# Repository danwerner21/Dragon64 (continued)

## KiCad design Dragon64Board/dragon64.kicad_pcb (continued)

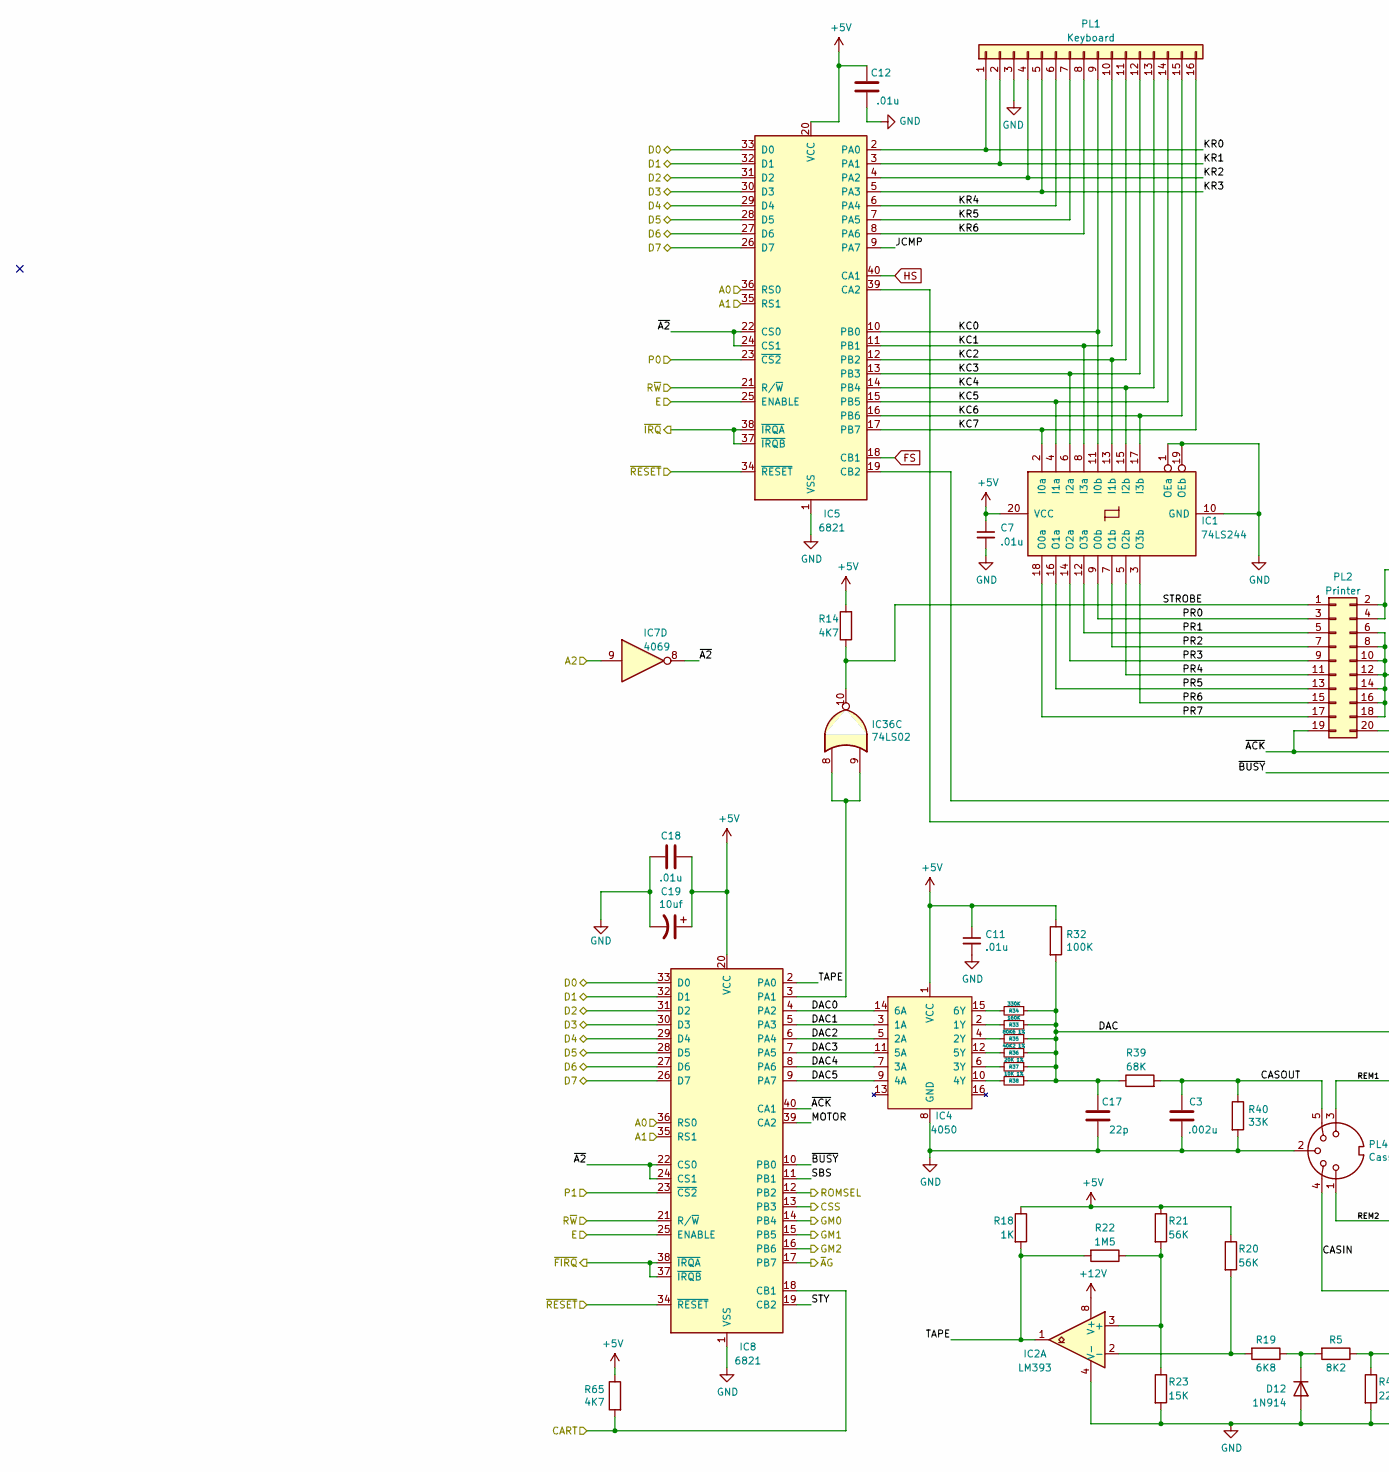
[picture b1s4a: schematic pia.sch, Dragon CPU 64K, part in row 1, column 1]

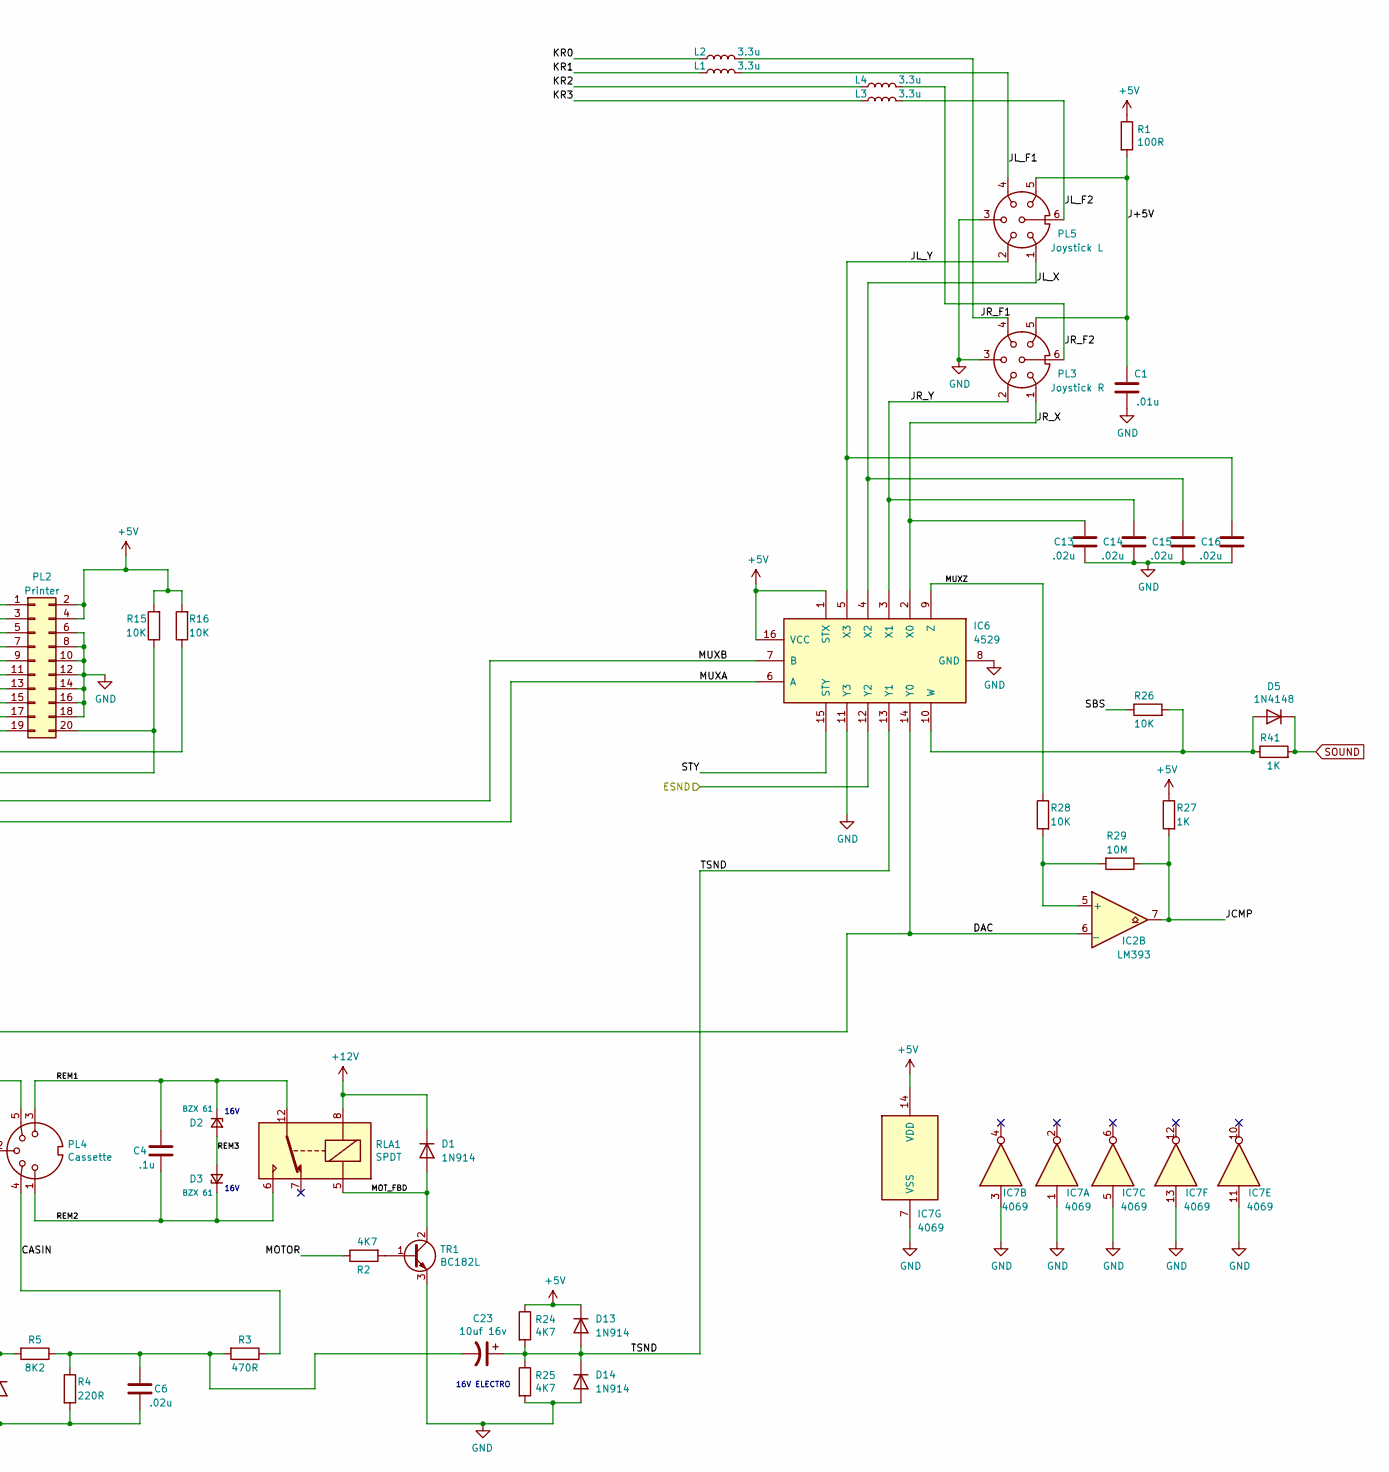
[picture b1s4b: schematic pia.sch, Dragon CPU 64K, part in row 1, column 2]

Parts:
C1, C7, C11, C12, C18: .01u; C_Disc_D7.5mm_W2.5mm_P5.00mm
C3: .002u; C_Disc_D7.5mm_W2.5mm_P5.00mm
C4: .1u; C_Disc_D7.5mm_W2.5mm_P5.00mm
C6, C13, C14, C15, C16: .02u; C_Disc_D7.5mm_W2.5mm_P5.00mm
C17: 22p; C_Disc_D7.5mm_W2.5mm_P5.00mm
C19: 10uf; CP_Radial_D4.0mm_P2.00mm
C23: 10uf 16v; CP_Radial_D4.0mm_P2.00mm
D1, D12, D13, D14: 1N914; D_DO-35_SOD27_P7.62mm_Horizontal
D2, D3: BZX 61; D_DO-35_SOD27_P7.62mm_Horizontal
D5: 1N4148; D_DO-35_SOD27_P7.62mm_Horizontal
IC1: 74LS244; DIP-20_W7.62mm_Socket_LongPads
IC2: LM393; DIP-8_W7.62mm_Socket_LongPads
IC4: 4050; DIP-16_W7.62mm_Socket_LongPads
IC5, IC8: 6821; DIP-40_W15.24mm_Socket_LongPads
IC6: 4529; DIP-16_W7.62mm_Socket_LongPads
IC7: 4069; DIP-14_W7.62mm_Socket_LongPads
IC36: 74LS02; DIP-14_W7.62mm_Socket_LongPads
L1, L2, L3, L4: 3.3u; L_Axial_L5.3mm_D2.2mm_P7.62mm_Horizontal_Vishay_IM-1
PL1: Keyboard; PinHeader_1x16_P2.54mm_Vertical
PL2: Printer; IDC-Header_2x10-1MP_P2.54mm_Latch_Horizontal
PL3: Joystick R; DIN-6_DELTRON_671-0601_Horizontal
PL4: Cassette; DIN-5_DELTRON_671-0501_45deg_Horizontal
PL5: Joystick L; DIN-6_DELTRON_671-0601_Horizontal
R1: 100R; R_Axial_DIN0207_L6.3mm_D2.5mm_P7.62mm_Horizontal
R2, R14, R24, R25, R65: 4K7; R_Axial_DIN0207_L6.3mm_D2.5mm_P7.62mm_Horizontal
R3: 470R; R_Axial_DIN0207_L6.3mm_D2.5mm_P7.62mm_Horizontal
R4: 220R; R_Axial_DIN0207_L6.3mm_D2.5mm_P7.62mm_Horizontal
R5: 8K2; R_Axial_DIN0207_L6.3mm_D2.5mm_P7.62mm_Horizontal
R15, R16, R26, R28: 10K; R_Axial_DIN0207_L6.3mm_D2.5mm_P7.62mm_Horizontal
R18, R27, R41: 1K; R_Axial_DIN0207_L6.3mm_D2.5mm_P7.62mm_Horizontal
R19: 6K8; R_Axial_DIN0207_L6.3mm_D2.5mm_P7.62mm_Horizontal
R20, R21: 56K; R_Axial_DIN0207_L6.3mm_D2.5mm_P7.62mm_Horizontal
R22: 1M5; R_Axial_DIN0207_L6.3mm_D2.5mm_P7.62mm_Horizontal
R23: 15K; R_Axial_DIN0207_L6.3mm_D2.5mm_P7.62mm_Horizontal
R29: 10M; R_Axial_DIN0207_L6.3mm_D2.5mm_P7.62mm_Horizontal
R32: 100K; R_Axial_DIN0207_L6.3mm_D2.5mm_P7.62mm_Horizontal
R33: 160K; R_Axial_DIN0207_L6.3mm_D2.5mm_P7.62mm_Horizontal
R34: 330K; R_Axial_DIN0207_L6.3mm_D2.5mm_P7.62mm_Horizontal
R35: 80K6 1%; R_Axial_DIN0207_L6.3mm_D2.5mm_P7.62mm_Horizontal
R36: 40K2 1%; R_Axial_DIN0207_L6.3mm_D2.5mm_P7.62mm_Horizontal
R37: 20K 1%; R_Axial_DIN0207_L6.3mm_D2.5mm_P7.62mm_Horizontal
R38: 10K 1%; R_Axial_DIN0207_L6.3mm_D2.5mm_P7.62mm_Horizontal
R39: 68K; R_Axial_DIN0207_L6.3mm_D2.5mm_P7.62mm_Horizontal
R40: 33K; R_Axial_DIN0207_L6.3mm_D2.5mm_P7.62mm_Horizontal
RLA1: SPDT; Relay_SPDT_HJR-4102
TR1: BC182L; TO-92

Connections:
+5V: C7.1, C11.1, C12.2, C18.2, C19.1, D13.1 (K), IC1.20 (VCC), IC4.1 (VCC), IC5.20 (VCC), IC6.1 (STX), IC6.16 (VCC), IC7.14 (VDD), IC8.20 (VCC), PL2.2, PL2.4, R1.1, R14.2, R15.2, R16.2, R18.1, R20.1, R21.1, R24.1, R27.1, R32.1, R65.1; also elsewhere on the board
+12V: D1.1 (K), IC2.8 (V+), RLA1.8; also elsewhere on the board
/ESND: IC6.12 (Y2); also elsewhere on the board
/P0: IC5.23 (~CS2); also elsewhere on the board
/P1: IC8.23 (~CS2); also elsewhere on the board
/PIAs/CASIN: PL4.4, R3.1
/PIAs/CASOUT: C3.2, PL4.5, R39.2, R40.1
/PIAs/CSS: IC8.13 (PB3); also elsewhere on the board
/PIAs/DAC: C17.2, IC2.6 (_), IC6.14 (Y0), R32.2, R33.1, R34.1, R35.1, R36.1, R37.1, R38.1, R39.1
/PIAs/DAC0: IC4.14 (6A), IC8.4 (PA2)
/PIAs/DAC1: IC4.3 (1A), IC8.5 (PA3)
/PIAs/DAC2: IC4.5 (2A), IC8.6 (PA4)
/PIAs/DAC3: IC4.11 (5A), IC8.7 (PA5)
/PIAs/DAC4: IC4.7 (3A), IC8.8 (PA6)
/PIAs/DAC5: IC4.9 (4A), IC8.9 (PA7)
/PIAs/GM0: IC8.14 (PB4); also elsewhere on the board
/PIAs/GM1: IC8.15 (PB5); also elsewhere on the board
/PIAs/GM2: IC8.16 (PB6); also elsewhere on the board
/PIAs/J+5V: C1.2, PL3.5, PL5.5, R1.2
/PIAs/JCMP: IC2.7, IC5.9 (PA7), R27.2, R29.1
/PIAs/JL_F1: L1.2, PL5.4
/PIAs/JL_F2: L3.2, PL5.6
/PIAs/JL_X: C15.2, IC6.4 (X2), PL5.1
/PIAs/JL_Y: C16.2, IC6.5 (X3), PL5.2
/PIAs/JR_F1: L2.2, PL3.4
/PIAs/JR_F2: L4.2, PL3.6
/PIAs/JR_X: C13.2, IC6.2 (X0), PL3.1
/PIAs/JR_Y: C14.2, IC6.3 (X1), PL3.2
/PIAs/KC0: IC1.11 (I0b), IC5.10 (PB0), PL1.9
/PIAs/KC1: IC1.8 (I3a), IC5.11 (PB1), PL1.10
/PIAs/KC2: IC1.13 (I1b), IC5.12 (PB2), PL1.11
/PIAs/KC3: IC1.6 (I2a), IC5.13 (PB3), PL1.12
/PIAs/KC4: IC1.15 (I2b), IC5.14 (PB4), PL1.13
/PIAs/KC5: IC1.4 (I1a), IC5.15 (PB5), PL1.14
/PIAs/KC6: IC1.17 (I3b), IC5.16 (PB6), PL1.15
/PIAs/KC7: IC1.2 (I0a), IC5.17 (PB7), PL1.16
/PIAs/KR0: IC5.2 (PA0), L2.1, PL1.1
/PIAs/KR1: IC5.3 (PA1), L1.1, PL1.2
/PIAs/KR2: IC5.4 (PA2), L4.1, PL1.4
/PIAs/KR3: IC5.5 (PA3), L3.1, PL1.5
/PIAs/KR4: IC5.6 (PA4), PL1.6
/PIAs/KR5: IC5.7 (PA5), PL1.7
/PIAs/KR6: IC5.8 (PA6), PL1.8
/PIAs/MOTOR: IC8.39 (CA2), R2.1
/PIAs/MOT_FBD: D1.2 (A), RLA1.5, TR1.2 (C)
/PIAs/MUXA: IC5.39 (CA2), IC6.6 (A)
/PIAs/MUXB: IC5.19 (CB2), IC6.7 (B)
/PIAs/MUXZ: IC6.9 (Z), R28.1
/PIAs/PR0: IC1.9 (O0b), PL2.3
/PIAs/PR1: IC1.12 (O3a), PL2.5
/PIAs/PR2: IC1.7 (O1b), PL2.7
/PIAs/PR3: IC1.14 (O2a), PL2.9
/PIAs/PR4: IC1.5 (O2b), PL2.11
/PIAs/PR5: IC1.16 (O1a), PL2.13
/PIAs/PR6: IC1.3 (O3b), PL2.15
/PIAs/PR7: IC1.18 (O0a), PL2.17
/PIAs/REM1: C4.2, D2.1 (K), PL4.3, RLA1.12
/PIAs/REM2: C4.1, D3.1 (K), PL4.1, RLA1.6
/PIAs/REM3: D2.2 (A), D3.2 (A)
/PIAs/SBS: IC8.11 (PB1), R26.1
/PIAs/STROBE: IC36.10, PL2.1, R14.1
/PIAs/STY: IC6.15 (STY), IC8.19 (CB2)
/PIAs/TAPE: IC2.1, IC8.2 (PA0), R18.2, R22.2
/PIAs/TSND: C23.1, D13.2 (A), D14.1 (K), IC6.13 (Y1), R24.2, R25.1
/PIAs/~A2: IC5.22 (CS0), IC5.24 (CS1), IC7.8, IC8.22 (CS0), IC8.24 (CS1)
/PIAs/~ACK: IC8.40 (CA1), PL2.19, R16.1
/PIAs/~A~G: IC8.17 (PB7); also elsewhere on the board
/PIAs/~BUSY: IC8.10 (PB0), PL2.20, R15.1
/ROMSEL: IC8.12 (PB2); also elsewhere on the board
/~FIRQ: IC8.37 (~IRQB), IC8.38 (~IRQA); also elsewhere on the board
/~IRQ: IC5.37 (~IRQB), IC5.38 (~IRQA); also elsewhere on the board
A0: IC5.36 (RS0), IC8.36 (RS0); also elsewhere on the board
A1: IC5.35 (RS1), IC8.35 (RS1); also elsewhere on the board
A2: IC7.9; also elsewhere on the board
CART: IC8.18 (CB1), R65.2; also elsewhere on the board
D0: IC5.33 (D0), IC8.33 (D0); also elsewhere on the board
D1: IC5.32 (D1), IC8.32 (D1); also elsewhere on the board
D2: IC5.31 (D2), IC8.31 (D2); also elsewhere on the board
D3: IC5.30 (D3), IC8.30 (D3); also elsewhere on the board
D4: IC5.29 (D4), IC8.29 (D4); also elsewhere on the board
D5: IC5.28 (D5), IC8.28 (D5); also elsewhere on the board
D6: IC5.27 (D6), IC8.27 (D6); also elsewhere on the board
D7: IC5.26 (D7), IC8.26 (D7); also elsewhere on the board
E: IC5.25 (ENABLE), IC8.25 (ENABLE); also elsewhere on the board
FS: IC5.18 (CB1); also elsewhere on the board
GND: C1.1, C3.1, C6.1, C7.2, C11.2, C12.1, C13.1, C14.1, C15.1, C16.1, C17.1, C18.1, C19.2, D12.2 (A), D14.2 (A), IC1.1 (OEa), IC1.10 (GND), IC1.19 (OEb), IC2.4 (V-), IC4.8 (GND), IC5.1 (VSS), IC6.8 (GND), IC6.11 (Y3), IC7.1, IC7.3, IC7.5, IC7.7 (VSS), IC7.11, IC7.13, IC8.1 (VSS), PL1.3, PL2.6, PL2.8, PL2.10, PL2.12, PL2.14, PL2.16, PL2.18, PL3.3, PL4.2, PL5.3, R4.2, R23.2, R25.2, R40.2, TR1.3 (E); also elsewhere on the board
HS: IC5.40 (CA1); also elsewhere on the board
unnamed: C6.2, C23.2, R3.2, R4.1, R5.1
unnamed: D5.2 (A), IC6.10 (W), R26.2, R41.1
unnamed: D12.1 (K), R5.2, R19.1
unnamed: IC2.2 (-), R19.2, R20.2
unnamed: IC2.3 (+), R21.2, R22.1, R23.1
unnamed: IC2.5 (+), R28.2, R29.2
unnamed: IC4.2 (1Y), R33.2
unnamed: IC4.4 (2Y), R35.2
unnamed: IC4.6 (3Y), R37.2
unnamed: IC4.10 (4Y), R38.2
unnamed: IC4.12 (5Y), R36.2
unnamed: IC4.15 (6Y), R34.2
unnamed: IC8.3 (PA1), IC36.8, IC36.9
unnamed: R2.2, TR1.1 (B)
R~W~: IC5.21 (R/~W), IC8.21 (R/~W); also elsewhere on the board
SOUND: D5.1 (K), R41.2; also elsewhere on the board
~RESET: IC5.34 (~RESET), IC8.34 (~RESET); also elsewhere on the board

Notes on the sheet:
16V
16V ELECTRO

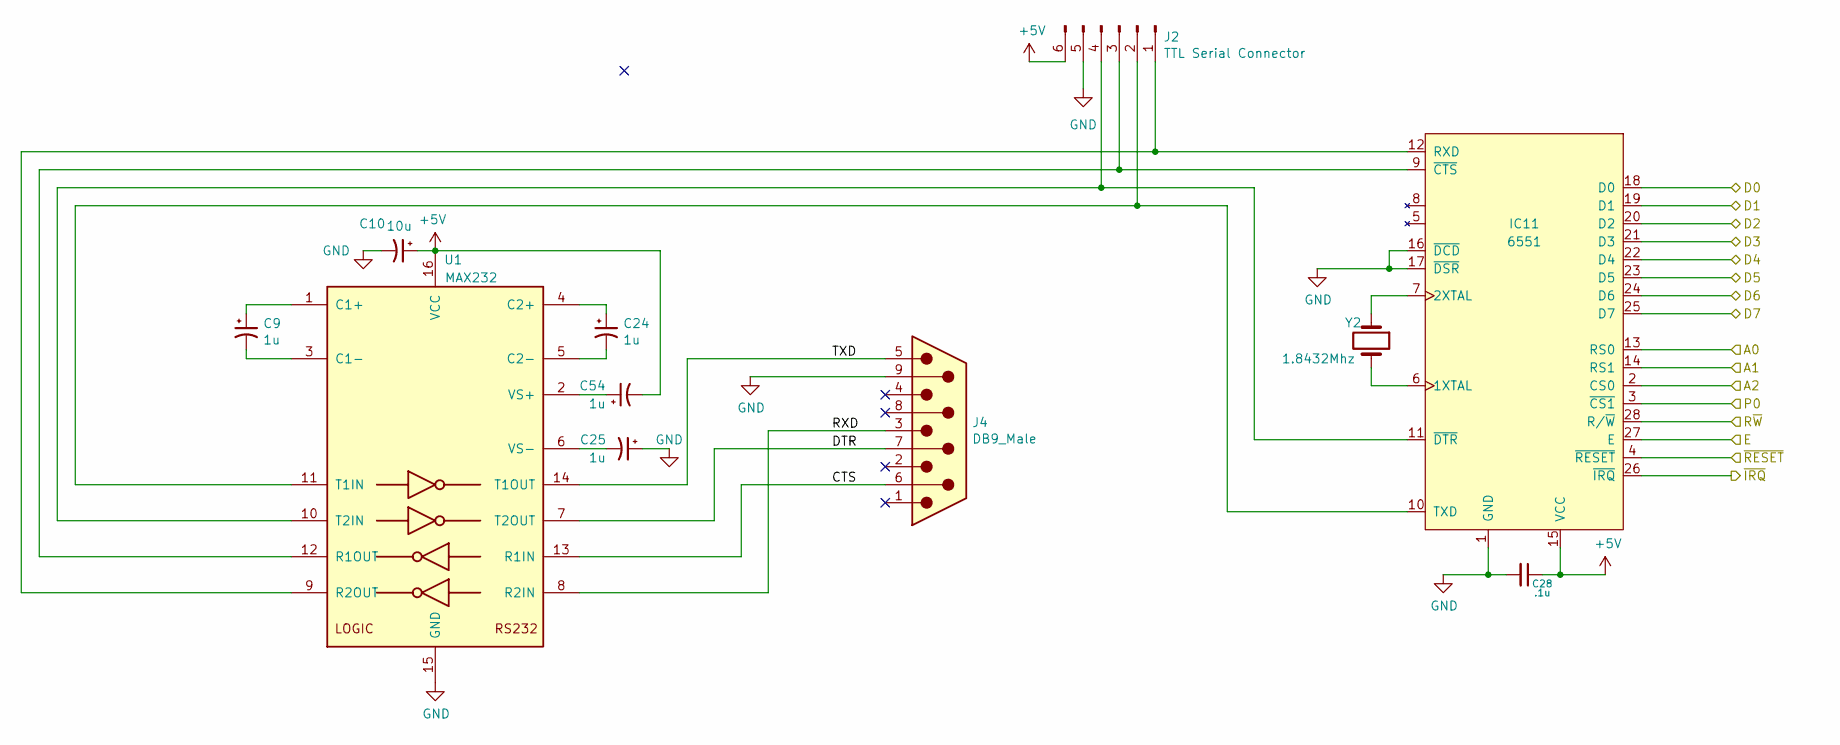
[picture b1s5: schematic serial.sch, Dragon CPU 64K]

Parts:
C9, C24, C25, C54: 1u; CP_Radial_D4.0mm_P2.00mm
C10: 10u; CP_Radial_D4.0mm_P2.00mm
C28: .1u; C_Disc_D7.5mm_W2.5mm_P5.00mm
IC11: 6551; DIP-28_W15.24mm_Socket_LongPads
J2: TTL Serial Connector; PinHeader_1x06_P2.54mm_Vertical
J4: DB9_Male; DSUB-9_Male_Horizontal_P2.77x2.84mm_EdgePinOffset4.94mm_Hou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
U1: MAX232; DIP-16_W7.62mm_Socket_LongPads
Y2: 1.8432Mhz; Crystal_HC49-U_Vertical

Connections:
+5V: C10.1, C28.1, C54.2, IC11.15 (VCC), J2.6, U1.16 (VCC); also elsewhere on the board
/P0: IC11.3 (~CS1~); also elsewhere on the board
/Serial/CTS: J4.6, U1.13 (R1IN)
/Serial/DTR: J4.7, U1.7 (T2OUT)
/Serial/RXD: J4.3, U1.8 (R2IN)
/Serial/TXD: J4.5, U1.14 (T1OUT)
/~IRQ: IC11.26 (~IRQ~); also elsewhere on the board
A0: IC11.13 (RS0); also elsewhere on the board
A1: IC11.14 (RS1); also elsewhere on the board
A2: IC11.2 (CS0); also elsewhere on the board
D0: IC11.18 (D0); also elsewhere on the board
D1: IC11.19 (D1); also elsewhere on the board
D2: IC11.20 (D2); also elsewhere on the board
D3: IC11.21 (D3); also elsewhere on the board
D4: IC11.22 (D4); also elsewhere on the board
D5: IC11.23 (D5); also elsewhere on the board
D6: IC11.24 (D6); also elsewhere on the board
D7: IC11.25 (D7); also elsewhere on the board
E: IC11.27 (E); also elsewhere on the board
GND: C10.2, C25.1, C28.2, IC11.1 (GND), IC11.16 (~DCD~), IC11.17 (~DSR~), J2.5, J4.9, U1.15 (GND); also elsewhere on the board
unnamed: C9.1, U1.1 (C1+)
unnamed: C9.2, U1.3 (C1-)
unnamed: C24.1, U1.4 (C2+)
unnamed: C24.2, U1.5 (C2-)
unnamed: C25.2, U1.6 (VS-)
unnamed: C54.1, U1.2 (VS+)
unnamed: IC11.6 (1XTAL), Y2.2
unnamed: IC11.7 (2XTAL), Y2.1
unnamed: IC11.9 (~CTS~), J2.3, U1.12 (R1OUT)
unnamed: IC11.10 (TXD), J2.2, U1.11 (T1IN)
unnamed: IC11.11 (~DTR~), J2.4, U1.10 (T2IN)
unnamed: IC11.12 (RXD), J2.1, U1.9 (R2OUT)
R~W~: IC11.28 (R/~W~); also elsewhere on the board
~RESET: IC11.4 (~RESET~); also elsewhere on the board

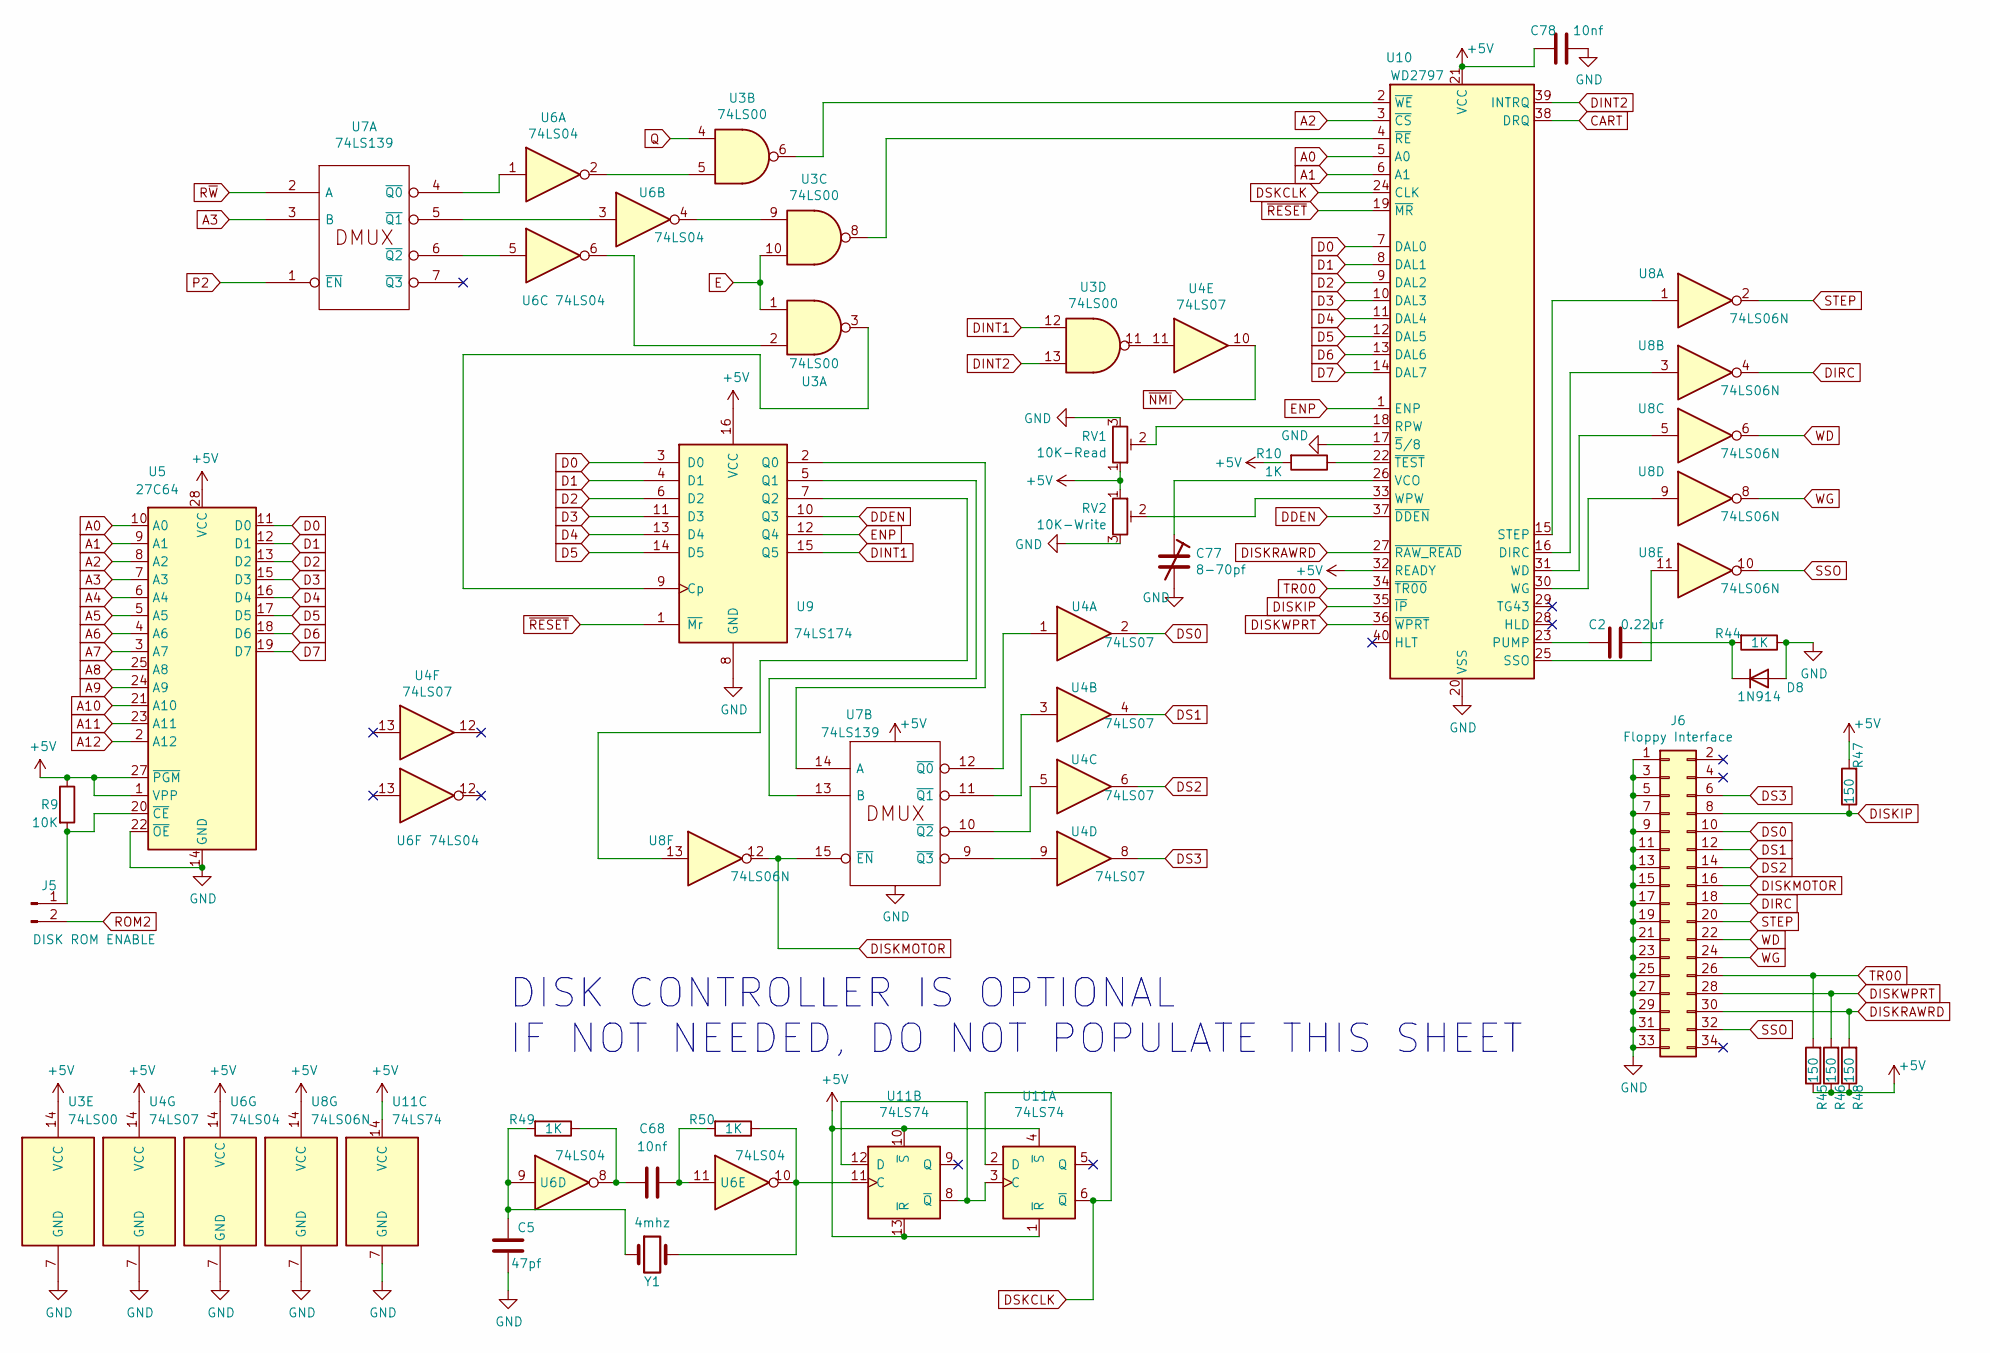
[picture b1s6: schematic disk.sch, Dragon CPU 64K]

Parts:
C2: 0.22uf; C_Disc_D7.5mm_W2.5mm_P5.00mm
C5: 47pf; C_Disc_D7.5mm_W2.5mm_P5.00mm
C68, C78: 10nf; C_Disc_D7.5mm_W2.5mm_P5.00mm
C77: 8-70pf; c_trimmer-10
D8: 1N914; D_DO-35_SOD27_P7.62mm_Horizontal
J5: DISK ROM ENABLE; PinHeader_1x02_P2.54mm_Vertical
J6: Floppy Interface; IDC-Header_2x17_P2.54mm_Vertical
R9: 10K; R_Axial_DIN0207_L6.3mm_D2.5mm_P7.62mm_Horizontal
R10, R44, R49, R50: 1K; R_Axial_DIN0207_L6.3mm_D2.5mm_P7.62mm_Horizontal
R45, R46, R47, R48: 150; R_Axial_DIN0207_L6.3mm_D2.5mm_P7.62mm_Horizontal
RV1: 10K-Read; Potentiometer_Vishay_T73YP_Vertical
RV2: 10K-Write; Potentiometer_Vishay_T73YP_Vertical
U3: 74LS00; DIP-14_W7.62mm_Socket_LongPads
U4: 74LS07; DIP-14_W7.62mm_Socket_LongPads
U5: 27C64; DIP-28_W15.24mm_Socket_LongPads
U6: 74LS04; DIP-14_W7.62mm_Socket_LongPads
U7: 74LS139; DIP-16_W7.62mm_Socket_LongPads
U8: 74LS06N; DIP-14_W7.62mm_Socket_LongPads
U9: 74LS174; DIP-16_W7.62mm_Socket_LongPads
U10: WD2797; DIP-40_W15.24mm
U11: 74LS74; DIP-14_W7.62mm_Socket_LongPads
Y1: 4mhz; Crystal_HC49-U_Vertical

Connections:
+5V: C78.2, R9.1, R10.2, R45.1, R46.1, R47.2, R48.1, RV1.1, RV2.1, U3.14 (VCC), U4.14 (VCC), U5.1 (VPP), U5.27 (~PGM), U5.28 (VCC), U6.14 (VCC), U7.16 (VCC), U8.14 (VCC), U9.16 (VCC), U10.21 (VCC), U10.32 (READY), U11.1 (~R), U11.4 (~S), U11.10 (~S), U11.13 (~R), U11.14 (VCC); also elsewhere on the board
A0: U5.10 (A0), U10.5 (A0); also elsewhere on the board
A1: U5.9 (A1), U10.6 (A1); also elsewhere on the board
A2: U5.8 (A2), U10.3 (~CS); also elsewhere on the board
A3: U5.7 (A3), U7.3 (B); also elsewhere on the board
A4: U5.6 (A4); also elsewhere on the board
A5: U5.5 (A5); also elsewhere on the board
A6: U5.4 (A6); also elsewhere on the board
A7: U5.3 (A7); also elsewhere on the board
A8: U5.25 (A8); also elsewhere on the board
A9: U5.24 (A9); also elsewhere on the board
A10: U5.21 (A10); also elsewhere on the board
A11: U5.23 (A11); also elsewhere on the board
A12: U5.2 (A12); also elsewhere on the board
CART: U10.38 (DRQ); also elsewhere on the board
D0: U5.11 (D0), U9.3 (D0), U10.7 (DAL0); also elsewhere on the board
D1: U5.12 (D1), U9.4 (D1), U10.8 (DAL1); also elsewhere on the board
D2: U5.13 (D2), U9.6 (D2), U10.9 (DAL2); also elsewhere on the board
D3: U5.15 (D3), U9.11 (D3), U10.10 (DAL3); also elsewhere on the board
D4: U5.16 (D4), U9.13 (D4), U10.11 (DAL4); also elsewhere on the board
D5: U5.17 (D5), U9.14 (D5), U10.12 (DAL5); also elsewhere on the board
D6: U5.18 (D6), U10.13 (DAL6); also elsewhere on the board
D7: U5.19 (D7), U10.14 (DAL7); also elsewhere on the board
DDEN: U9.10 (Q3), U10.37 (~DDEN)
DINT1: U3.12, U9.15 (Q5)
DINT2: U3.13, U10.39 (INTRQ)
DIRC: J6.18, U8.4
DISKIP: J6.8, R47.1, U10.35 (~IP)
DISKMOTOR: J6.16, U7.15 (~EN), U8.12
DISKRAWRD: J6.30, R48.2, U10.27 (~RAW_READ)
DISKWPRT: J6.28, R46.2, U10.36 (~WPRT)
DS0: J6.10, U4.2
DS1: J6.12, U4.4
DS2: J6.14, U4.6
DS3: J6.6, U4.8
DSKCLK: U10.24 (CLK), U11.2 (D), U11.6 (~Q)
E: U3.1, U3.10; also elsewhere on the board
ENP: U9.12 (Q4), U10.1 (ENP)
GND: C5.1, C77.2, C78.1, D8.2 (A), J6.1, J6.3, J6.5, J6.7, J6.9, J6.11, J6.13, J6.15, J6.17, J6.19, J6.21, J6.23, J6.25, J6.27, J6.29, J6.31, J6.33, R44.1, RV1.3, RV2.3, U3.7 (GND), U4.7 (GND), U5.14 (GND), U5.22 (~OE), U6.7 (GND), U7.8 (GND), U8.7 (GND), U9.8 (GND), U10.17 (~5~/8), U10.20 (VSS), U11.7 (GND); also elsewhere on the board
unnamed: C2.1, D8.1 (K), R44.2
unnamed: C2.2, U10.23 (PUMP)
unnamed: C5.2, R49.2, U6.9, Y1.1
unnamed: C68.1, R50.2, U6.11
unnamed: C68.2, R49.1, U6.8
unnamed: C77.1, U10.26 (VCO)
unnamed: J5.1, R9.2, U5.20 (~CE)
unnamed: R10.1, U10.22 (~TEST)
unnamed: R50.1, U6.10, U11.11 (C), Y1.2
unnamed: RV1.2, U10.18 (RPW)
unnamed: RV2.2, U10.33 (WPW)
unnamed: U3.2, U6.6
unnamed: U3.3, U9.9 (Cp)
unnamed: U3.5, U6.2
unnamed: U3.9, U6.4
unnamed: U3.11, U4.11
unnamed: U4.1, U7.12 (~Q0)
unnamed: U4.3, U7.11 (~Q1)
unnamed: U4.5, U7.10 (~Q2)
unnamed: U4.9, U7.9 (~Q3)
unnamed: U6.1, U7.4 (~Q0)
unnamed: U6.3, U7.5 (~Q1)
unnamed: U6.5, U7.6 (~Q2)
unnamed: U7.13 (B), U9.5 (Q1)
unnamed: U7.14 (A), U9.2 (Q0)
unnamed: U8.13, U9.7 (Q2)
unnamed: U3.6, U10.2 (~WE)
unnamed: U3.8, U10.4 (~RE)
unnamed: U8.1, U10.15 (STEP)
unnamed: U8.3, U10.16 (DIRC)
unnamed: U8.11, U10.25 (SSO)
unnamed: U8.9, U10.30 (WG)
unnamed: U8.5, U10.31 (WD)
unnamed: U11.3 (C), U11.8 (~Q), U11.12 (D)
P2: U7.1 (~EN); also elsewhere on the board
Q: U3.4; also elsewhere on the board
ROM2: J5.2; also elsewhere on the board
R~W~: U7.2 (A); also elsewhere on the board
SSO: J6.32, U8.10
STEP: J6.20, U8.2
TR00: J6.26, R45.2, U10.34 (~TR00)
WD: J6.22, U8.6
WG: J6.24, U8.8
~NMI: U4.10; also elsewhere on the board
~RESET: U9.1 (~Mr), U10.19 (~MR); also elsewhere on the board

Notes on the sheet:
DISK CONTROLLER IS OPTIONAL IF NOT NEEDED, DO NOT POPULATE THIS SHEET

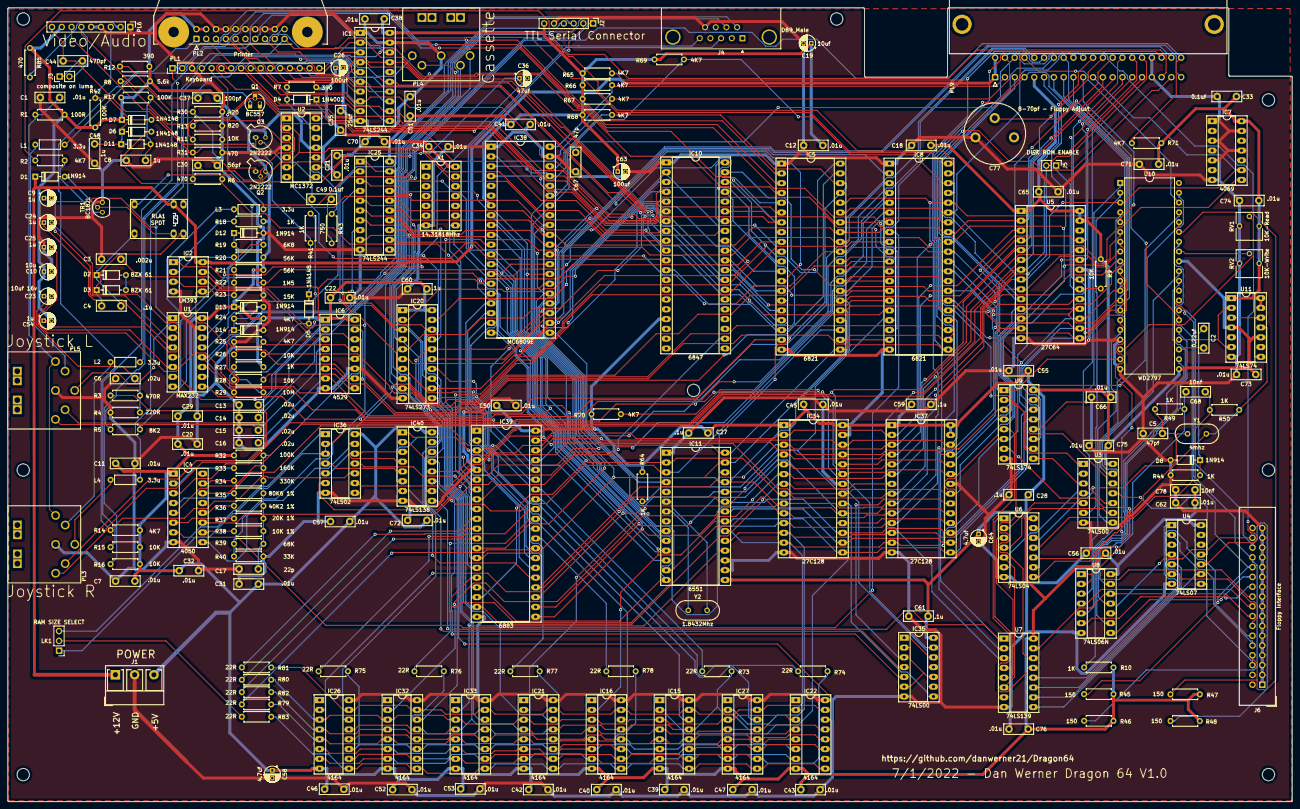
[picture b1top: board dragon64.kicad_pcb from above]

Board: 2 copper layers, 333.2 x 205.9 mm, 232 parts (1 on the bottom side), 266 nets.

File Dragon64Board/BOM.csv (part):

QTY,ref,value,part,description
1,IC4,4050,4050,
1,IC7,4069,4069,Hex inverter
8,"IC15,IC16,IC21,IC22,IC26,IC27,IC32,IC33",4164,4164,
1,IC6,4529,4529,
1,IC11,6551,6551,
2,"IC5,IC8",6821,6821,"Peripheral Interface Adapter 1MHz, DIP-40"
1,IC10,6847,6847,
1,IC39,6883,6883,
1,D8,1N914,1N914,"100V 0.3A Small Signal Fast Switching Diode, DO-35"
2,"IC34,ic37",27C128,27C128,"OTP EPROM 128 KiBit, [Obsolete 2004-01]"
1,U5,27C64,27C64,"OTP EPROM 64 KiBit, [Obsolete 2004-01]"
2,"IC35,U3",74LS00,74LS00,quad 2-input NAND gate
1,IC36,74LS02,74LS02,quad 2-input NOR gate
1,U6,74LS04,74LS04,Hex Inverter
1,U8,74LS06N,74LS06N,Inverter Open Collect
1,U4,74LS07,74LS07,Hex Buffers and Drivers With Open Collector High Voltage Outputs
1,IC40,74LS138,74LS138,Decoder 3 to 8 active low outputs
1,U7,74LS139,74LS139,"Dual Decoder 1 of 4, Active low outputs"
1,U9,74LS174,74LS174,"Hex D-type Flip-Flop, reset"
2,"IC1,IC25",74LS244,74LS244,"Octal Buffer and Line Driver With 3-State Output, active-low enables, non-inverting outputs"
1,IC20,74LS273,74LS273,"8-bit D Flip-Flop, reset"
1,J1,ATX,ATX-20,ATX Power supply 20pins
1,C3,.002u,C,Unpolarized capacitor
37,"C1,C7,C11,C12,C18,C20,C21,C22,C29,C31,C32,C34,C38,C39,C40,C41,C42,C43,C45,C46,C47,C50,C51,C52,C53,C55,C56,C57,C62,C65,C66,C70,C71,C72,C73,C74,C75,C76",.01u,C,Unpolarized capacitor
5,"C6,C13,C14,C15,C16",.02u,C,Unpolarized capacitor
11,"C2,C27,C33,C4,C49,C5,C59,C60,C61,C68,C69",.1u,C,Unpolarized capacitor
2,"C33,C49",0.1uf,C,Unpolarized capacitor
1,C37,100pf,C,Unpolarized capacitor
1,C78,10nf,C,Unpolarized capacitor
2,"C8,C48",1u,C,Unpolarized capacitor
1,C17,22p,C,Unpolarized capacitor
1,C35,25uf,C,Unpolarized capacitor
1,C44,470pf,C,Unpolarized capacitor
1,C67,47p,C,Unpolarized capacitor
1,C30,56pf,C,Unpolarized capacitor
1,C10,10u,C_Polarized_Small_US,"Polarized capacitor, small US symbol"
4,"C9,C24,C25,C54",1u,C_Polarized_Small_US,"Polarized capacitor, small US symbol"
1,"C26,C63",100uf,C_Polarized_US,"Polarized capacitor, US symbol"
1,C19,10uf,C_Polarized_US,"Polarized capacitor, US symbol"
1,C23,10uf 16v,C_Polarized_US,"Polarized capacitor, US symbol"
2,"C58,C64",4.7uf,C_Polarized_US,"Polarized capacitor, US symbol"
1,C36,47uf,C_Polarized_US,"Polarized capacitor, US symbol"
2,"C11,C7",.01u,C_Small,"Unpolarized capacitor, small symbol"
1,C77,8-70pf,C_Trim,Trimmable capacitor
1,J3,composite on luma,Conn_01x02_Male,"Generic connector, single row, 01x02, script generated (kicad-library-utils/schlib/autogen/connector/)"
1,J5,DISK ROM ENABLE,Conn_01x02_Male,"Generic connector, single row, 01x02, script generated (kicad-library-utils/schlib/autogen/connector/)"
1,J2,TTL Serial Connector,Conn_01x06_Male,"Generic connector, single row, 01x06, script generated (kicad-library-utils/schlib/autogen/connector/)"
1,PL6,Power/Video,Conn_01x09,"Generic connector, single row, 01x09, script generated (kicad-library-utils/schlib/autogen/connector/)"
1,PL1,Keyboard,Conn_01x16,"Generic connector, single row, 01x16, script generated (kicad-library-utils/schlib/autogen/connector/)"
1,PL2,Printer,Conn_02x10_Odd_Even,"Generic connector, double row, 02x10, odd/even pin numbering scheme (row 1 odd numbers, row 2 even numbers), script generated (kicad-library-utils/schlib/autogen/connector/)"
1,J6,Floppy Interface,Conn_02x17_Odd_Even,"Generic connector, double row, 02x17, odd/even pin numbering scheme (row 1 odd numbers, row 2 even numbers), script generated (kicad-library-utils/schlib/autogen/connector/)"
1,PL7,Cartridge,Conn_02x20_Odd_Even,"Generic connector, double row, 02x20, odd/even pin numbering scheme (row 1 odd numbers, row 2 even numbers), script generated (kicad-library-utils/schlib/autogen/connector/)"
1,PL9,Cartridge,Conn_02x20_Odd_Even,"Generic connector, double row, 02x20, odd/even pin numbering scheme (row 1 odd numbers, row 2 even numbers), script generated (kicad-library-utils/schlib/autogen/connector/)"
1,Y2,1.8432Mhz,Crystal,Two pin crystal
1,X1,14.31818Mhz,CXO_DIP14,"Crystal Clock Oscillator, DIP14-style metal package"
1,D4,1N4002,D,Diode
4,"D5,D6,D7,D11",1N4148,D,Diode
4,"D1,D12,D13,D14",1N914,D,Diode
2,"D2,D3",BZX 61,D_Zener_Small,"Zener diode, small symbol"
1,J4,DB9_Male,DB9_Male,9-pin male D-SUB connector
1,PL4,Cassette,DIN-5_180degree,5-pin DIN connector (5-pin DIN-5 stereo)
2,"PL3,PL5",Joystick L,DIN-6,6-pin DIN connector
1,LK1,~,Jumper_3_Bridged12,"Jumper, 3-pole, pins 1+2 closed/bridged"
4,"L1,L2,L3,L4",3.3u,L,Inductor
1,IC2,LM393,LM393,"Low-Power, Low-Offset Voltage, Dual Comparators, DIP-8/SOIC-8/TO-99-8"
1,U1,MAX232,MAX232,"Dual RS232 driver/receiver, 5V supply, 120kb/s, 0C-70C"
1,U2,MC1372,MC1372,
1,IC38,MC6809E,MC6809E,
2,"Q2,Q3",2N2222,Q_NPN_BCE,"NPN transistor, base/collector/emitter"
1,TR1,BC182L,Q_NPN_BCE,"NPN transistor, base/collector/emitter"
1,Q1,BC557,Q_PNP_BCE,"PNP transistor, base/collector/emitter"
4,"R45,R46,R47,R48",150,R,Resistor
2,"R7,R12",390,R,Resistor
1,R30,420,R,Resistor
3,"R6,R31,R85",470,R,Resistor
1,R43,750,R,Resistor
1,R13,820,R,Resistor
3,"R17,R32,R42",100K,R,Resistor
1,R1,100R,R,Resistor
6,"R9,R11,R15,R16,R26,R28",10K,R,Resistor
1,R29,10M,R,Resistor
1,R23,15K,R,Resistor
6,"R10,R18,R27,R41,R44,R64",1K,R,Resistor
1,R22,1M5,R,Resistor
1,R4,220R,R,Resistor
11,"R73,R74,R75,R76,R77,R78,R79,R80,R81,R82,R83",22R,R,Resistor
1,R40,33K,R,Resistor
1,R3,470R,R,Resistor
11,"R14,R2,R24,R25,R65,R66,R67,R68,R69,R70,R71",4K7,R,Resistor
1,R8,5.6k,R,Resistor
2,"R20,R21",56K,R,Resistor
1,R39,68K,R,Resistor
1,R19,6K8,R,Resistor
1,R5,8K2,R,Resistor
2,"RV1,RV2",10K-Read,R_Potentiometer_Trim,Trim-potentiometer
1,R38,10K 1%,R_Small,"Resistor, small symbol"
1,R33,160K,R_Small,"Resistor, small symbol"
1,R37,20K 1%,R_Small,"Resistor, small symbol"
1,R34,330K,R_Small,"Resistor, small symbol"
1,R36,40K2 1%,R_Small,"Resistor, small symbol"
1,R35,80K6 1%,R_Small,"Resistor, small symbol"
1,RLA1,SPDT,TIANBO-HJR-4102-L,"TIANBO HJR-4102-L, Single Pole Relay, 5mm Pitch, 3A"
1,U10,WD2797,WD2797,"Floppy disk controller, DIP-40"
1,X3,4Mhz,XO91,HCMOS Clock Oscillator
,,,,
,,,,
,,,,
,,,,
,,,,
,,,,
,,,,
,,,,
,,,,
,,,,
,,,,
,,,,
,,,,
,,,,
,,,,
,,,,
,,,,
,,,,
,,,,
,,,,
,,,,
,,,,
,,,,
,,,,
,,,,
,,,,
,,,,
,,,,
,,,,
,,,,
,,,,
,,,,
,,,,
,,,,
,,,,
,,,,
,,,,
,,,,
,,,,
,,,,
,,,,
,,,,
,,,,
,,,,
,,,,
,,,,
,,,,
,,,,
,,,,
,,,,
,,,,
,,,,
,,,,
,,,,
,,,,
,,,,
,,,,
,,,,
,,,,
,,,,
,,,,
,,,,
,,,,
,,,,
,,,,
,,,,
,,,,
,,,,
,,,,
,,,,
,,,,
,,,,
,,,,
,,,,
,,,,
,,,,
,,,,
,,,,
,,,,
,,,,
,,,,
,,,,
,,,,
,,,,
,,,,
,,,,
,,,,
,,,,
,,,,
,,,,
,,,,
,,,,
,,,,
,,,,
,,,,
,,,,
,,,,
,,,,
,,,,
,,,,
,,,,
,,,,
,,,,
,,,,
,,,,
,,,,
,,,,
,,,,
,,,,
,,,,
,,,,
,,,,
,,,,
,,,,
,,,,
,,,,
,,,,
,,,,
,,,,
,,,,
,,,,
,,,,
,,,,
,,,,
,,,,
,,,,
,,,,
,,,,
,,,,
,,,,
,,,,
,,,,
,,,,
,,,,
,,,,
,,,,
,,,,
,,,,
,,,,
,,,,
,,,,
,,,,
,,,,
,,,,
,,,,
,,,,
,,,,
,,,,
,,,,
,,,,
,,,,
,,,,
,,,,
,,,,
,,,,
,,,,
,,,,
,,,,
,,,,
,,,,
,,,,
,,,,
,,,,
,,,,
,,,,
,,,,
,,,,
,,,,
,,,,
,,,,
,,,,
,,,,
,,,,
,,,,
,,,,
,,,,
,,,,
,,,,
,,,,
,,,,
,,,,
,,,,
,,,,
,,,,
,,,,
,,,,
,,,,
,,,,
,,,,
,,,,
,,,,
,,,,
,,,,
,,,,
,,,,
,,,,
,,,,
,,,,
,,,,
,,,,
,,,,
,,,,
,,,,
,,,,
,,,,
,,,,
,,,,
,,,,
,,,,
,,,,
,,,,
,,,,
,,,,
,,,,
,,,,
,,,,
,,,,
,,,,
,,,,
,,,,
,,,,
,,,,
,,,,
,,,,
,,,,
,,,,
,,,,
,,,,
,,,,
,,,,
,,,,
,,,,
,,,,
,,,,
,,,,
,,,,
,,,,
,,,,
,,,,
,,,,
,,,,
,,,,
,,,,
,,,,
,,,,
,,,,
,,,,
,,,,
,,,,
,,,,
,,,,
,,,,
,,,,
,,,,
,,,,
,,,,
,,,,
,,,,
,,,,
,,,,
,,,,
,,,,
,,,,
,,,,
,,,,
,,,,
,,,,
,,,,
,,,,
,,,,
,,,,
,,,,
,,,,
,,,,
,,,,
,,,,
,,,,
,,,,
,,,,
,,,,
,,,,
,,,,
,,,,
,,,,
,,,,
,,,,
,,,,
,,,,
,,,,
,,,,
,,,,
,,,,
,,,,
,,,,
,,,,
,,,,
,,,,
,,,,
,,,,
,,,,
,,,,
,,,,
,,,,
,,,,
,,,,
,,,,
,,,,
,,,,
,,,,
,,,,
,,,,
,,,,
,,,,
,,,,
,,,,
,,,,
,,,,
,,,,
,,,,
,,,,
,,,,
,,,,
,,,,
,,,,
,,,,
,,,,
,,,,
,,,,
,,,,
,,,,
,,,,
,,,,
,,,,
,,,,
,,,,
,,,,
,,,,
,,,,
,,,,
,,,,
,,,,
,,,,
,,,,
,,,,
,,,,
,,,,
,,,,
,,,,
,,,,
,,,,
,,,,
,,,,
,,,,
,,,,
,,,,
,,,,
,,,,
,,,,
,,,,
,,,,
,,,,
,,,,
,,,,
,,,,
,,,,
,,,,
,,,,
,,,,
,,,,
,,,,
,,,,
,,,,
,,,,
,,,,
,,,,
,,,,
,,,,
,,,,
,,,,
,,,,
,,,,
,,,,
,,,,
,,,,
,,,,
,,,,
,,,,
,,,,
,,,,
,,,,
,,,,
,,,,
,,,,
,,,,
,,,,
,,,,
,,,,
,,,,
,,,,
,,,,
,,,,
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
